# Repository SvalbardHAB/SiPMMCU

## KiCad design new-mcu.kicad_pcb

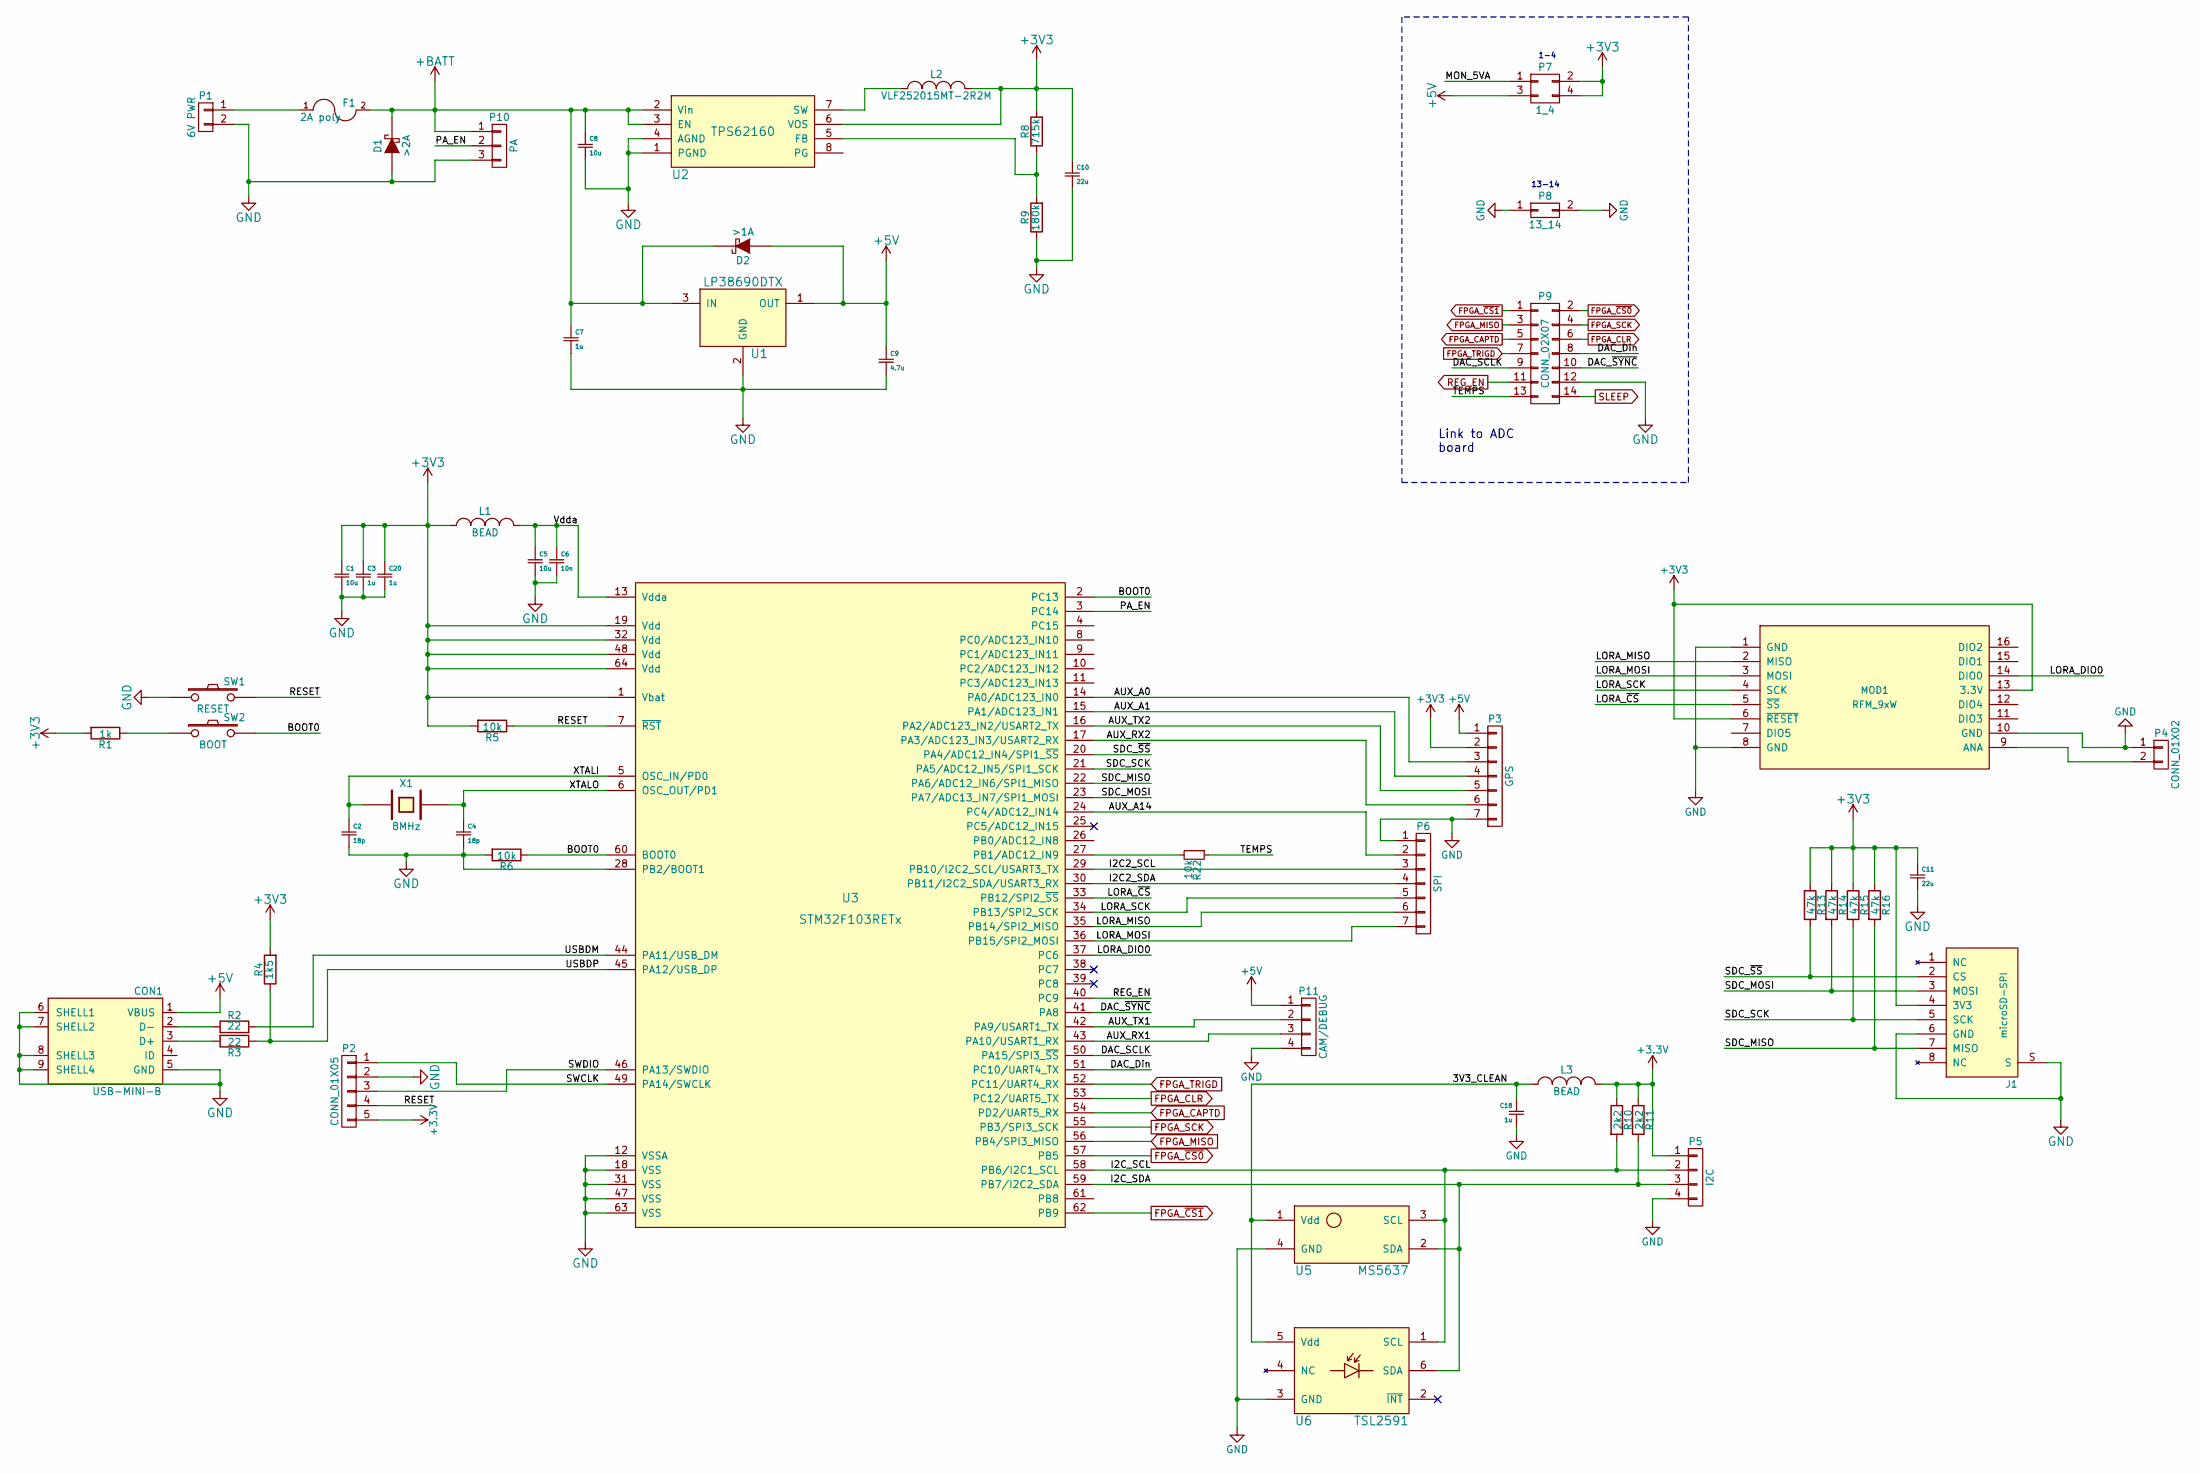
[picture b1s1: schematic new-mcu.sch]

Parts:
C1, C5, C8: 10u; C_0805
C2, C4: 18p; C_0402
C3, C7, C20: 1u; C_0603
C6: 10n; C_0201
C9: 4.7u; C_0805
C10, C11: 22u; C_1206
C18: 1u; C_0805
CON1: USB-MINI-B; USB_Mini-B
D1: >2A; SOD-123
D2: >1A; SOD-123
F1: 2A poly; Fuse_SMD1206_Reflow
J1: microSD-SPI; DM3CS-SF
L1, L3: BEAD; R_0603
L2: VLF252015MT-2R2M; Neosid_Inductor_SM-NE29_SMD1008
MOD1: RFM_9xW; RFM9xW
P1: 6V PWR; Pin_Header_Straight_1x02
P2: CONN_01X05; Pin_Header_Straight_1x05
P3: GPS; Pin_Header_Straight_1x07
P4: CONN_01X02; Pin_Header_Straight_1x02
P5: I2C; Pin_Header_Straight_1x04
P6: SPI; Pin_Header_Straight_1x07
P7: 1_4; Pin_Header_Straight_2x02
P8: 13_14; Pin_Header_Straight_2x01
P9: CONN_02X07; Pin_Header_Straight_2x07
P10: PA; Pin_Header_Straight_1x03
P11: CAM/DEBUG; Pin_Header_Straight_1x04
R1: 1k; R_0402
R2, R3: 22; R_0402
R4: 1k5; R_0402
R5, R6, R22: 10k; R_0402
R8: 715k; R_0402
R9: 180k; R_0402
R10, R11: 2k2; R_0402
R13, R14, R15, R16: 47k; R_0402
SW1: RESET; SKSCLDE010
SW2: BOOT; SKSCLDE010
U1: LP38690DTX; TO-252-2Lead
U2: TPS62160; MSOP-8_3x3mm_Pitch0.65mm
U3: STM32F103RETx; LQFP-64_10x10mm_Pitch0.5mm-HS
U5: MS5637
U6: TSL2591; SON-6
X1: 8MHz; XTAL-TXC-5x3.2

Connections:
+5V: C9.1, CON1.1 (VBUS), D2.1 (A), P3.1, P7.3, P11.1, U1.1 (OUT)
+BATT: C7.1, C8.1, D1.2 (K), D2.2 (K), F1.2, P10.1, U1.3 (IN), U2.2 (Vin), U2.3 (EN)
/3V3_CLEAN: C18.1, L3.2, U5.1 (Vdd), U6.5 (Vdd)
/AUX_A0: P3.3, U3.14 (PA0/ADC123_IN0)
/AUX_A1: P3.4, U3.15 (PA1/ADC123_IN1)
/AUX_A14: P6.2, U3.24 (PC4/ADC12_IN14)
/AUX_RX1: P11.3, U3.43 (PA10/USART1_RX)
/AUX_RX2: P3.6, U3.17 (PA3/ADC123_IN3/USART2_RX)
/AUX_TX1: P11.2, U3.42 (PA9/USART1_TX)
/AUX_TX2: P3.5, U3.16 (PA2/ADC123_IN2/USART2_TX)
/BOOT0: R6.1, SW2.2, U3.2 (PC13), U3.60 (BOOT0)
/DAC_Din: P9.8, U3.51 (PC10/UART4_TX)
/DAC_SCLK: P9.9, U3.50 (PA15/SPI3_~SS)
/DAC_~SYNC: P9.10, U3.41 (PA8)
/I2C2_SCL: P6.3, U3.29 (PB10/I2C2_SCL/USART3_TX)
/I2C2_SDA: P6.4, U3.30 (PB11/I2C2_SDA/USART3_RX)
/I2C_SCL: P5.2, R10.2, U3.58 (PB6/I2C1_SCL), U5.3 (SCL), U6.1 (SCL)
/I2C_SDA: P5.3, R11.2, U3.59 (PB7/I2C2_SDA), U5.2 (SDA), U6.6 (SDA)
/LORA_DIO0: MOD1.14 (DIO0), U3.37 (PC6)
/LORA_MISO: MOD1.2 (MISO), P6.6, U3.35 (PB14/SPI2_MISO)
/LORA_MOSI: MOD1.3 (MOSI), P6.7, U3.36 (PB15/SPI2_MOSI)
/LORA_SCK: MOD1.4 (SCK), P6.5, U3.34 (PB13/SPI2_SCK)
/LORA_~CS: MOD1.5 (~SS), U3.33 (PB12/SPI2_~SS)
/MON_5VA: P7.1
/PA_EN: P10.2, U3.3 (PC14)
/RESET: P2.4, R5.1, SW1.2, U3.7 (~RST)
/SDC_MISO: J1.7 (MISO), R16.2, U3.22 (PA6/ADC12_IN6/SPI1_MISO)
/SDC_MOSI: J1.3 (MOSI), R14.2, U3.23 (PA7/ADC13_IN7/SPI1_MOSI)
/SDC_SCK: J1.5 (SCK), R15.2, U3.21 (PA5/ADC12_IN5/SPI1_SCK)
/SDC_~SS: J1.2 (CS), R13.2, U3.20 (PA4/ADC12_IN4/SPI1_~SS)
/SWCLK: P2.1, U3.49 (PA14/SWCLK)
/SWDIO: P2.3, U3.46 (PA13/SWDIO)
/TEMPS: P9.13, R22.1
/USBDM: R2.2, U3.44 (PA11/USB_DM)
/USBDP: R3.1, R4.1, U3.45 (PA12/USB_DP)
/Vdda: C5.1, C6.1, L1.2, U3.13 (Vdda)
/XTALI: C2.1, U3.5 (OSC_IN/PD0), X1.1
/XTALO: C4.1, U3.6 (OSC_OUT/PD1), X1.2
FPGA_CAPTD: P9.5, U3.54 (PD2/UART5_RX)
FPGA_CLR: P9.6, U3.53 (PC12/UART5_TX)
FPGA_MISO: P9.3, U3.56 (PB4/SPI3_MISO)
FPGA_SCK: P9.4, U3.55 (PB3/SPI3_SCK)
FPGA_TRIGD: P9.7, U3.52 (PC11/UART4_RX)
FPGA_~CS0: P9.2, U3.57 (PB5)
FPGA_~CS1: P9.1, U3.62 (PB9)
GND: C1.2, C2.2, C3.2, C4.2, C5.2, C6.2, C7.2, C8.2, C9.2, C10.2, C11.2, C18.2, C20.2, CON1.5 (GND), CON1.6 (SHELL1), CON1.7 (SHELL2), CON1.8 (SHELL3), CON1.9 (SHELL4), D1.1 (A), J1.6 (GND), J1.S, MOD1.1 (GND), MOD1.8 (GND), MOD1.10 (GND), P1.2, P2.2, P3.7, P4.1, P5.4, P6.1, P8.1, P8.2, P9.12, P10.3, P11.4, R6.2, R9.1, SW1.1, U1.2 (GND), U2.1 (PGND), U2.4 (AGND), U3.12 (VSSA), U3.18 (VSS), U3.28 (PB2/BOOT1), U3.31 (VSS), U3.47 (VSS), U3.63 (VSS), U5.4 (GND), U6.3 (GND)
unnamed: CON1.2 (D-), R2.1
unnamed: CON1.3 (D+), R3.2
unnamed: F1.1, P1.1
unnamed: L2.1, U2.7 (SW)
unnamed: MOD1.9 (ANA), P4.2
unnamed: R1.1, SW2.1
unnamed: R8.1, R9.2, U2.5 (FB)
unnamed: R22.2, U3.27 (PB1/ADC12_IN9)
REG_EN: P9.11, U3.40 (PC9)
SLEEP: P9.14

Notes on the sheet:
1-4
13-14
Link to ADC board

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
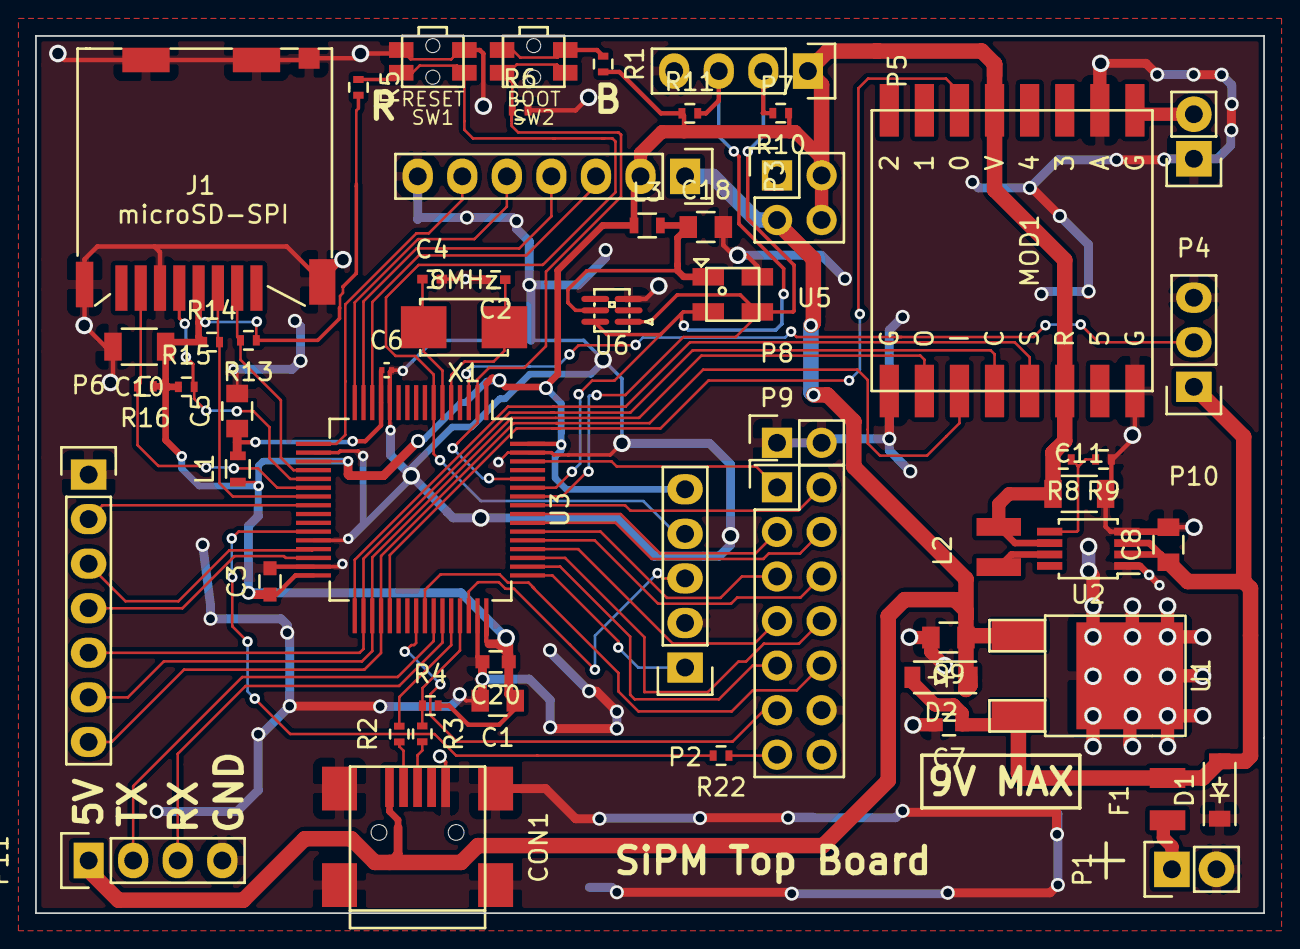
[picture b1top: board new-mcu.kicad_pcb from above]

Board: 2 copper layers, 70.0 x 50.0 mm, 56 parts (0 on the bottom side), 55 nets.

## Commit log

2016-07-07 Add new MCU board for SiPM assembly (non-essential)
